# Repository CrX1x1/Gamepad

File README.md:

|Reference	|Qty	|Value	|DNP	|Exclude from BOM	|Exclude from Board	|Footprint	|Datasheet|
|-|-|-|-|-|-|-|-|
|A1,D16,E1,ESC1,N1-N3,Q1,R1,S1,W1	|11	|SW_Push	|	|	|	|Button_Switch_Keyboard:SW_Cherry_MX_1.00u_PCB	|
|CTRL1	|1	|SW_Push	|	|	|	|Button_Switch_Keyboard:SW_Cherry_MX_1.25u_PCB	|
|D1-D15	|15	|D_Small	|	|	|	|Diode_THT:D_DO-35_SOD27_P10.16mm_Horizontal	|
|RGB1-RGB15	|15	|SK6812MINI-E	|	|	|	|footprints:SK6812MINI-E_fixed	|https://cdn-shop.adafruit.com/product-files/4960/4960_SK6812MINI-E_REV02_EN.pdf
|SHIFT1	|1	|SW_Push	|	|	|	|Button_Switch_Keyboard:SW_Cherry_MX_2.25u_PCB	|
|SPACE1	|1	|SW_Push	|	|	|	|Button_Switch_Keyboard:SW_Cherry_MX_6.25u_PCB	|
|TAB1	|1	|SW_Push	|	|	|	|Button_Switch_Keyboard:SW_Cherry_MX_1.50u_PCB	|
|U1	|1	|MOUDLE-SEEEDUINO-XIAO	|	|	|	|footprints:XIAO-Generic-Hybrid-14P-2.54-21X17.8MM	|

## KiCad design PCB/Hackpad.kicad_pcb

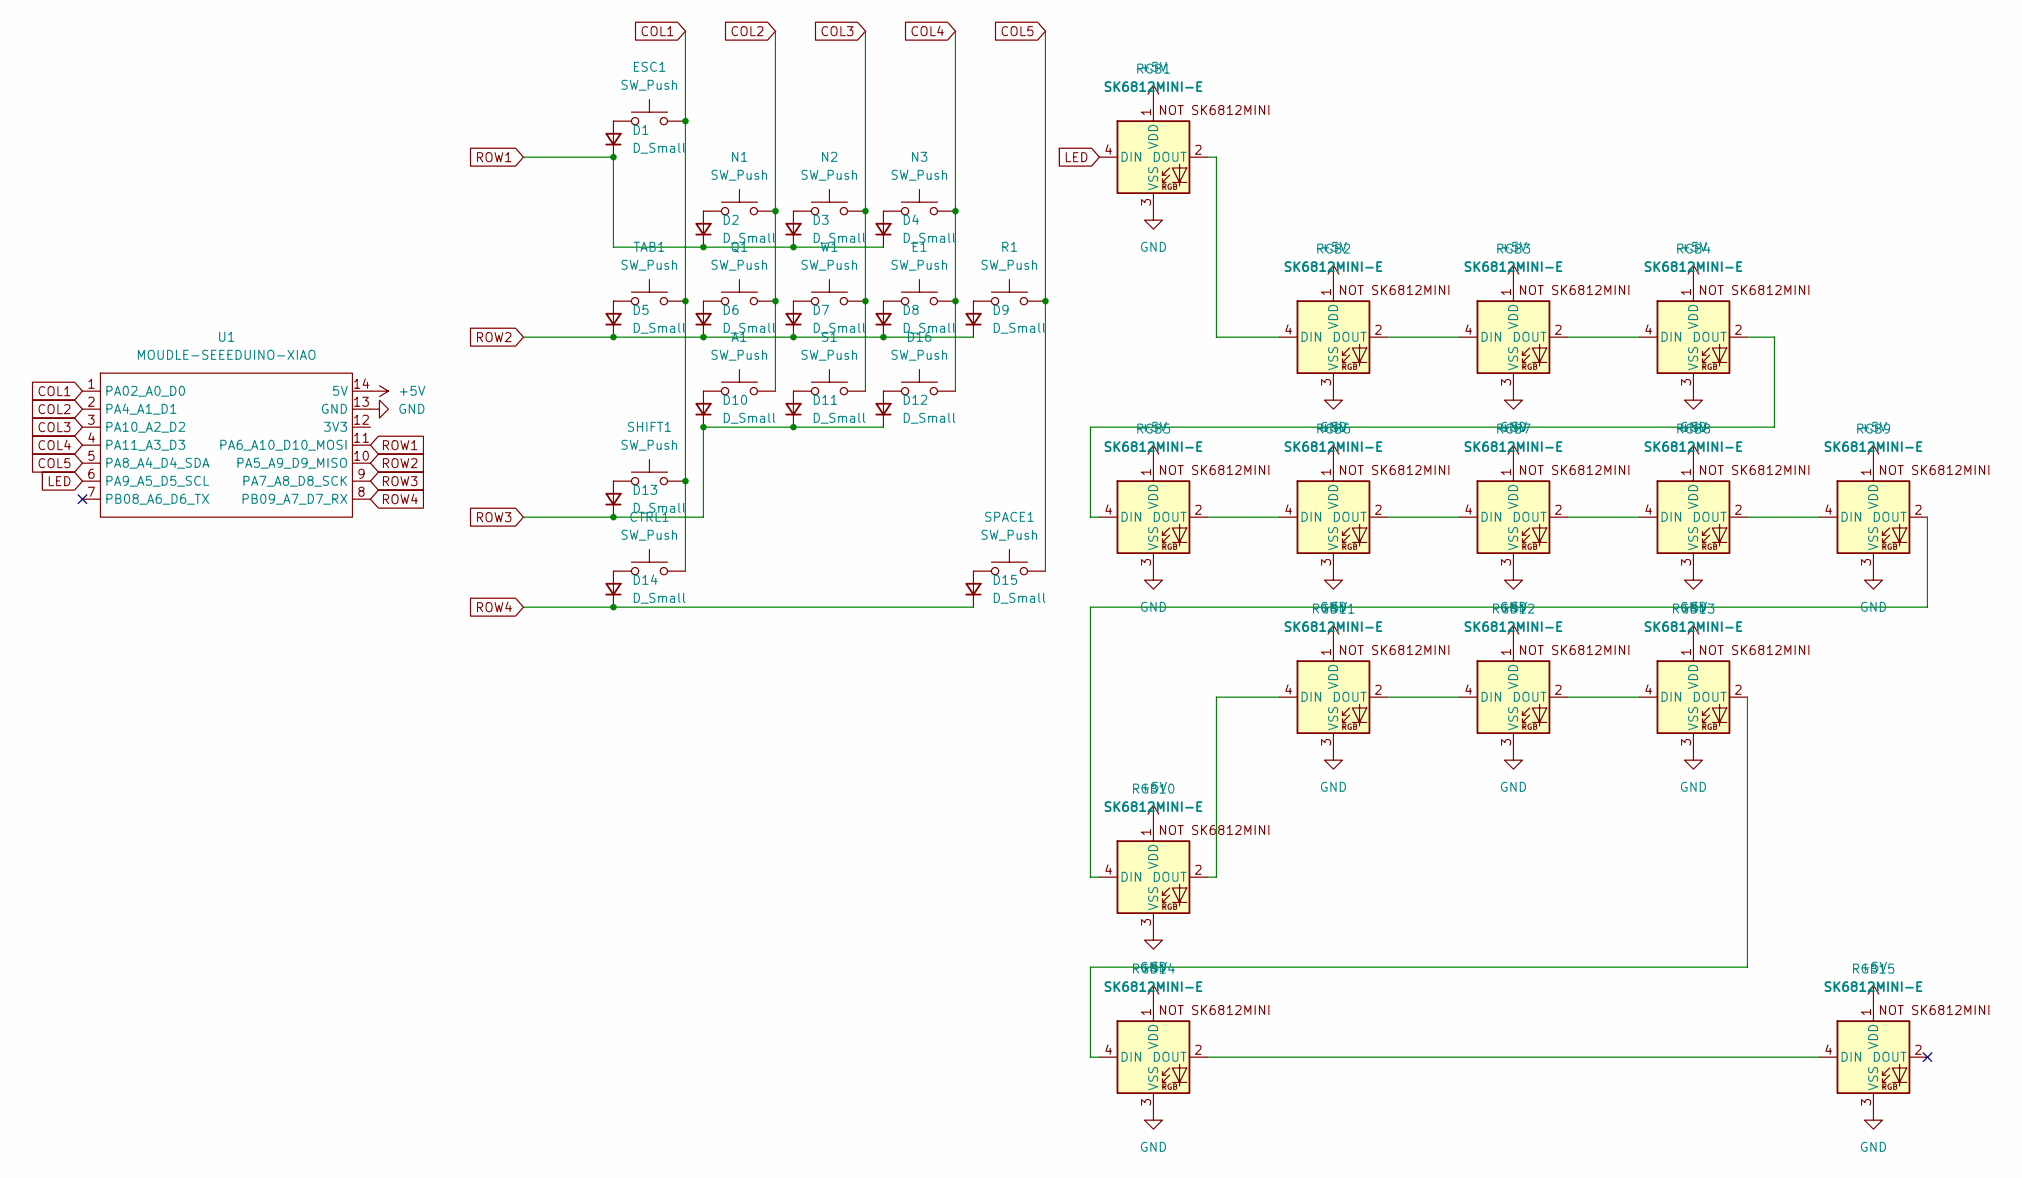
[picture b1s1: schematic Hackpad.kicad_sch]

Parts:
A1: SW_Push; SW_Cherry_MX_1.00u_PCB
CTRL1: SW_Push; SW_Cherry_MX_1.25u_PCB
D1, D2, D3, D4, D5, D6, D7, D8, D9, D10, D11, D12, D13, D14, D15: D_Small; D_DO-35_SOD27_P10.16mm_Horizontal
D16: SW_Push; SW_Cherry_MX_1.00u_PCB
E1: SW_Push; SW_Cherry_MX_1.00u_PCB
ESC1: SW_Push; SW_Cherry_MX_1.00u_PCB
N1, N2, N3: SW_Push; SW_Cherry_MX_1.00u_PCB
Q1: SW_Push; SW_Cherry_MX_1.00u_PCB
R1: SW_Push; SW_Cherry_MX_1.00u_PCB
RGB1, RGB2, RGB3, RGB4, RGB5, RGB6, RGB7, RGB8, RGB9, RGB10, RGB11, RGB12, RGB13, RGB14, RGB15: SK6812MINI-E; SK6812MINI-E_fixed
S1: SW_Push; SW_Cherry_MX_1.00u_PCB
SHIFT1: SW_Push; SW_Cherry_MX_2.25u_PCB
SPACE1: SW_Push; SW_Cherry_MX_6.25u_PCB
TAB1: SW_Push; SW_Cherry_MX_1.50u_PCB
U1: MOUDLE-SEEEDUINO-XIAO; XIAO-Generic-Hybrid-14P-2.54-21X17.8MM
W1: SW_Push; SW_Cherry_MX_1.00u_PCB

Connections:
+5V: RGB1.1 (VDD), RGB2.1 (VDD), RGB3.1 (VDD), RGB4.1 (VDD), RGB5.1 (VDD), RGB6.1 (VDD), RGB7.1 (VDD), RGB8.1 (VDD), RGB9.1 (VDD), RGB10.1 (VDD), RGB11.1 (VDD), RGB12.1 (VDD), RGB13.1 (VDD), RGB14.1 (VDD), RGB15.1 (VDD), U1.14 (5V)
COL1: CTRL1.2, ESC1.2, SHIFT1.2, TAB1.2, U1.1 (PA02_A0_D0)
COL2: A1.2, N1.2, Q1.2, U1.2 (PA4_A1_D1)
COL3: N2.2, S1.2, U1.3 (PA10_A2_D2), W1.2
COL4: D16.2, E1.2, N3.2, U1.4 (PA11_A3_D3)
COL5: R1.2, SPACE1.2, U1.5 (PA8_A4_D4_SDA)
GND: RGB1.3 (VSS), RGB2.3 (VSS), RGB3.3 (VSS), RGB4.3 (VSS), RGB5.3 (VSS), RGB6.3 (VSS), RGB7.3 (VSS), RGB8.3 (VSS), RGB9.3 (VSS), RGB10.3 (VSS), RGB11.3 (VSS), RGB12.3 (VSS), RGB13.3 (VSS), RGB14.3 (VSS), RGB15.3 (VSS), U1.13 (GND)
LED: RGB1.4 (DIN), U1.6 (PA9_A5_D5_SCL)
unnamed: D1.2 (A), ESC1.1
unnamed: D2.2 (A), N1.1
unnamed: D3.2 (A), N2.1
unnamed: D4.2 (A), N3.1
unnamed: D5.2 (A), TAB1.1
unnamed: D6.2 (A), Q1.1
unnamed: D7.2 (A), W1.1
unnamed: D8.2 (A), E1.1
unnamed: D9.2 (A), R1.1
unnamed: A1.1, D10.2 (A)
unnamed: D11.2 (A), S1.1
unnamed: D12.2 (A), D16.1
unnamed: D13.2 (A), SHIFT1.1
unnamed: CTRL1.1, D14.2 (A)
unnamed: D15.2 (A), SPACE1.1
unnamed: RGB1.2 (DOUT), RGB2.4 (DIN)
unnamed: RGB2.2 (DOUT), RGB3.4 (DIN)
unnamed: RGB3.2 (DOUT), RGB4.4 (DIN)
unnamed: RGB4.2 (DOUT), RGB5.4 (DIN)
unnamed: RGB5.2 (DOUT), RGB6.4 (DIN)
unnamed: RGB6.2 (DOUT), RGB7.4 (DIN)
unnamed: RGB7.2 (DOUT), RGB8.4 (DIN)
unnamed: RGB8.2 (DOUT), RGB9.4 (DIN)
unnamed: RGB9.2 (DOUT), RGB10.4 (DIN)
unnamed: RGB10.2 (DOUT), RGB11.4 (DIN)
unnamed: RGB11.2 (DOUT), RGB12.4 (DIN)
unnamed: RGB12.2 (DOUT), RGB13.4 (DIN)
unnamed: RGB13.2 (DOUT), RGB14.4 (DIN)
unnamed: RGB14.2 (DOUT), RGB15.4 (DIN)
ROW1: D1.1 (K), D2.1 (K), D3.1 (K), D4.1 (K), U1.11 (PA6_A10_D10_MOSI)
ROW2: D5.1 (K), D6.1 (K), D7.1 (K), D8.1 (K), D9.1 (K), U1.10 (PA5_A9_D9_MISO)
ROW3: D10.1 (K), D11.1 (K), D12.1 (K), D13.1 (K), U1.9 (PA7_A8_D8_SCK)
ROW4: D14.1 (K), D15.1 (K), U1.8 (PB09_A7_D7_RX)

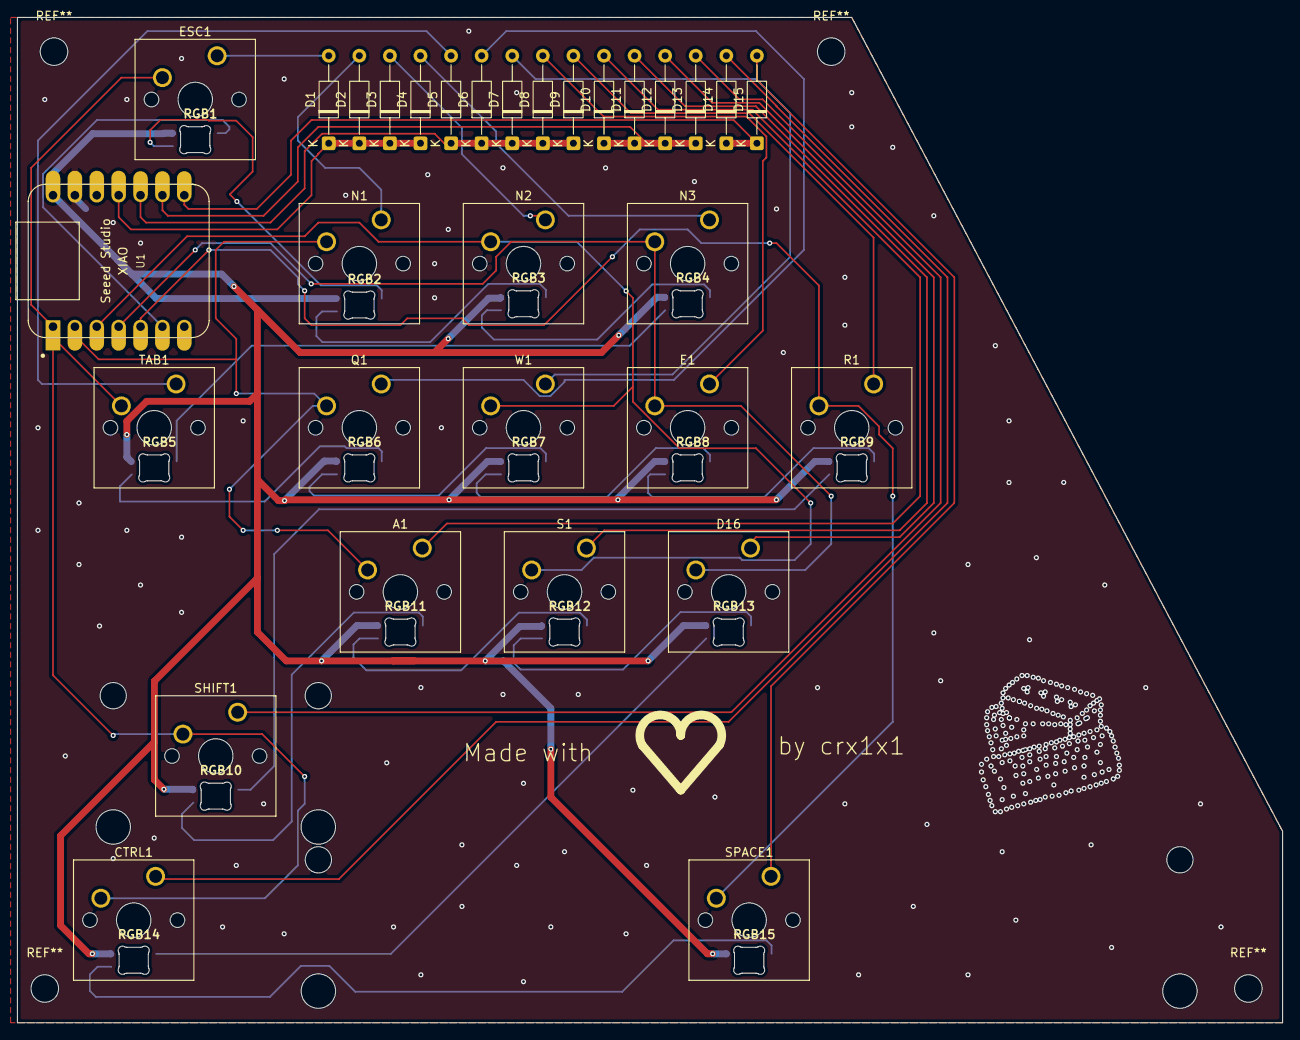
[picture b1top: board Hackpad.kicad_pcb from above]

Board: 2 copper layers, 146.8 x 116.6 mm, 46 parts (0 on the bottom side), 41 nets.

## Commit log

2026-06-05 Initial commit
    Made a bunch of progress, but totally forget to commit
2026-06-06 Rev 1.0
    idk
2026-06-09 3d model and firmware compiled
2026-06-09 Ship 1
2026-06-09 organized images
2026-06-09 test
2026-06-09 edit readme
2026-06-09 edit readme
    edited
